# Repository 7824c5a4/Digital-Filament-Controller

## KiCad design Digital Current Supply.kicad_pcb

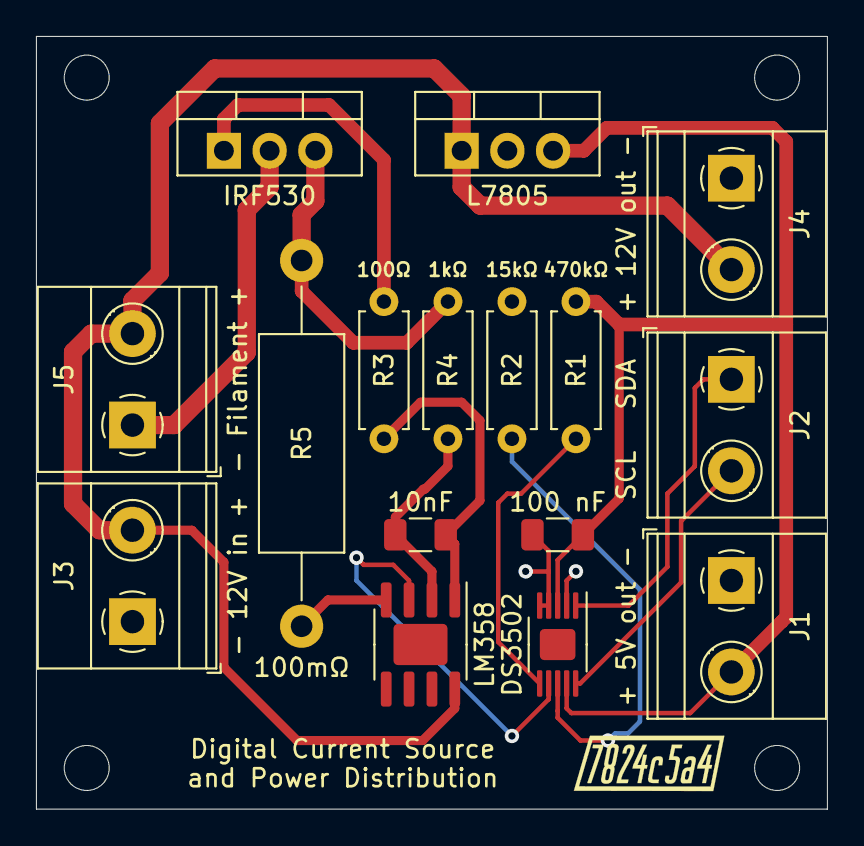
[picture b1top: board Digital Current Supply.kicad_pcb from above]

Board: 2 copper layers, 43.9 x 42.9 mm, 16 parts (0 on the bottom side), 13 nets.

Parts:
C1: 100 nF; C_1206_3216Metric
C2: 10nF; C_1206_3216Metric
J1: 5vout; TerminalBlock_Phoenix_MKDS-1,5-2-5.08_1x02_P5.08mm_Horizont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
J2: i2c; TerminalBlock_Phoenix_MKDS-1,5-2-5.08_1x02_P5.08mm_Horizont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
J3: 12vin; TerminalBlock_Phoenix_MKDS-1,5-2-5.08_1x02_P5.08mm_Horizont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
J4: 12vout; TerminalBlock_Phoenix_MKDS-1,5-2-5.08_1x02_P5.08mm_Horizont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
J5: FILout; TerminalBlock_Phoenix_MKDS-1,5-2-5.08_1x02_P5.08mm_Horizont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
Q1: IRF530; TO-220-3_Vertical
R1: 470kΩ; R_Axial_DIN0207_L6.3mm_D2.5mm_P7.62mm_Horizontal
R2: 15kΩ; R_Axial_DIN0207_L6.3mm_D2.5mm_P7.62mm_Horizontal
R3: 1kΩ; R_Axial_DIN0207_L6.3mm_D2.5mm_P7.62mm_Horizontal
R4: 100Ω; R_Axial_DIN0207_L6.3mm_D2.5mm_P7.62mm_Horizontal
R5: 100mΩ; R_Axial_DIN0414_L11.9mm_D4.5mm_P20.32mm_Horizontal
U1: L7805; TO-220-3_Vertical
U2: DS3502; MSOP-10-1EP_3x3mm_P0.5mm_EP1.73x1.98mm
U3: LM358; SOIC-8-1EP_3.9x4.9mm_P1.27mm_EP2.29x3mm

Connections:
+5V: C1.1, J1.2, R1.1, U1.3, U2.3, U2.9
+12V: J3.2, J4.2, J5.2, U1.1, U3.8
/lm358inv: C2.2, R3.1, U3.2
FILin: J5.1, Q1.2
GND: C1.2, J1.1, J3.1, J4.1, R2.1, R5.1, U1.2, U2.2, U2.4, U2.5, U3.4
unnamed: C2.1, R4.2, U3.1
unnamed: Q1.1, R4.1
unnamed: Q1.3, R3.2, R5.2
unnamed: R1.2, U2.6
unnamed: R2.2, U2.8
RH: U2.7, U3.3
SCL: J2.2, U2.10
SDA: J2.1, U2.1

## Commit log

2020-02-10 Removed netlist file
